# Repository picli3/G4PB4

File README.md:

# G4PB4

Proyecto de hardware en PCB desarrollado en KiCad, pensado como base para integración electrónica específica según la aplicación del diseño.

## Qué incluye
- esquemáticos o archivos de diseño en KiCad
- PCB o documentación asociada
- base reutilizable para análisis, fabricación o mejora del proyecto

## Propósito general
Este repositorio busca concentrar el diseño de hardware del proyecto en un formato editable y reutilizable, facilitando pruebas, documentación y futuras iteraciones del circuito.

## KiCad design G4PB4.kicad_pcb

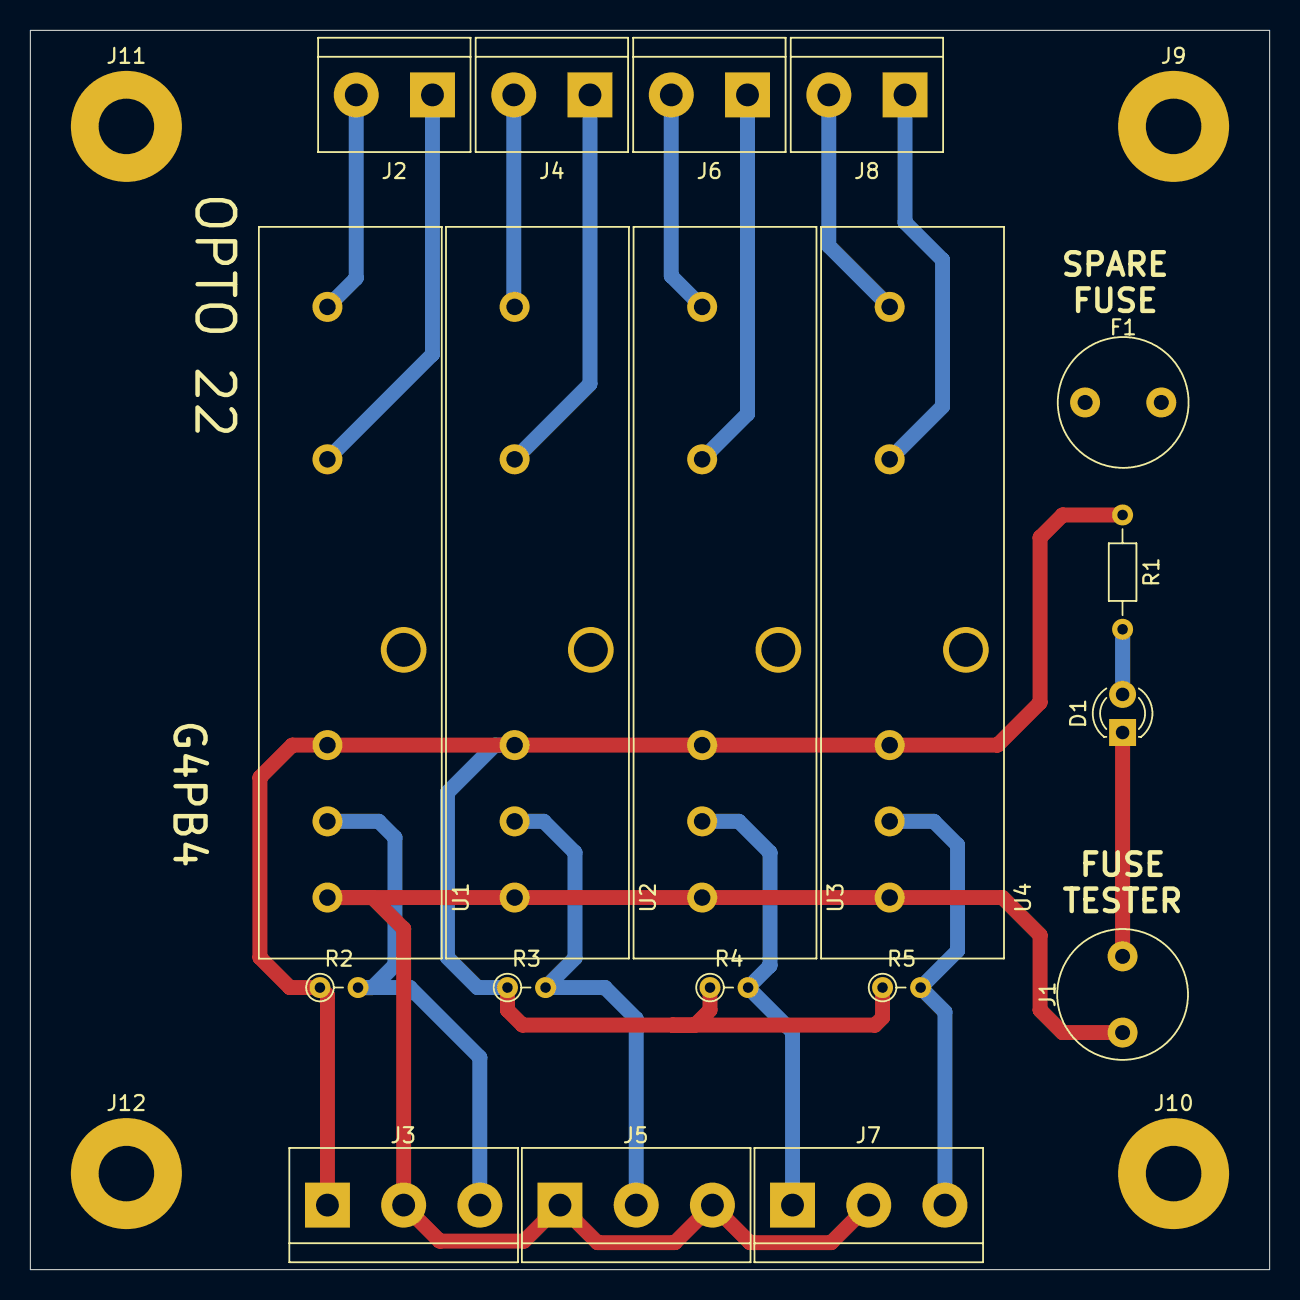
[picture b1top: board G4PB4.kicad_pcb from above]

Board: 2 copper layers, 82.6 x 82.6 mm, 23 parts (0 on the bottom side), 16 nets.

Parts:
D1: LED; LED_D3.0mm
F1: Fuse; Fuse_Littelfuse_372_D8.50mm
J1: Conn_01x02; Fuse_Littelfuse_372_D8.50mm
J2, J4, J6, J8: Conn_01x02; TerminalBlock_bornier-2_P5.08mm
J3, J5, J7: Conn_01x03; TerminalBlock_bornier-3_P5.08mm
J9, J10, J11, J12: Conn_01x01; MountingHole_3.7mm_Pad
R1: R; R_Axial_DIN0204_L3.6mm_D1.6mm_P7.62mm_Horizontal
R2, R3, R4, R5: R; R_Axial_DIN0204_L3.6mm_D1.6mm_P2.54mm_Vertical
U1, U2, U3, U4: G4ODC5; MA-Models

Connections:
unnamed: D1.1, J1.2
unnamed: D1.2, R1.2
unnamed: J1.1, J3.2, J5.1, J5.3, J7.2, U1.5, U2.5, U3.5, U4.5
unnamed: J2.1, U1.2
unnamed: J2.2, U1.1
unnamed: J3.1, R1.1, R2.1, R3.1, R4.1, R5.1, U1.3, U2.3, U3.3, U4.3
unnamed: J3.3, R2.2, U1.4
unnamed: J4.1, U2.2
unnamed: J4.2, U2.1
unnamed: J5.2, R3.2, U2.4
unnamed: J6.1, U3.2
unnamed: J6.2, U3.1
unnamed: J7.1, R4.2, U3.4
unnamed: J7.3, R5.2, U4.4
unnamed: J8.1, U4.2
unnamed: J8.2, U4.1

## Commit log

2020-10-13 primera version creada
2026-04-29 Agrega README con descripción inicial del proyecto
